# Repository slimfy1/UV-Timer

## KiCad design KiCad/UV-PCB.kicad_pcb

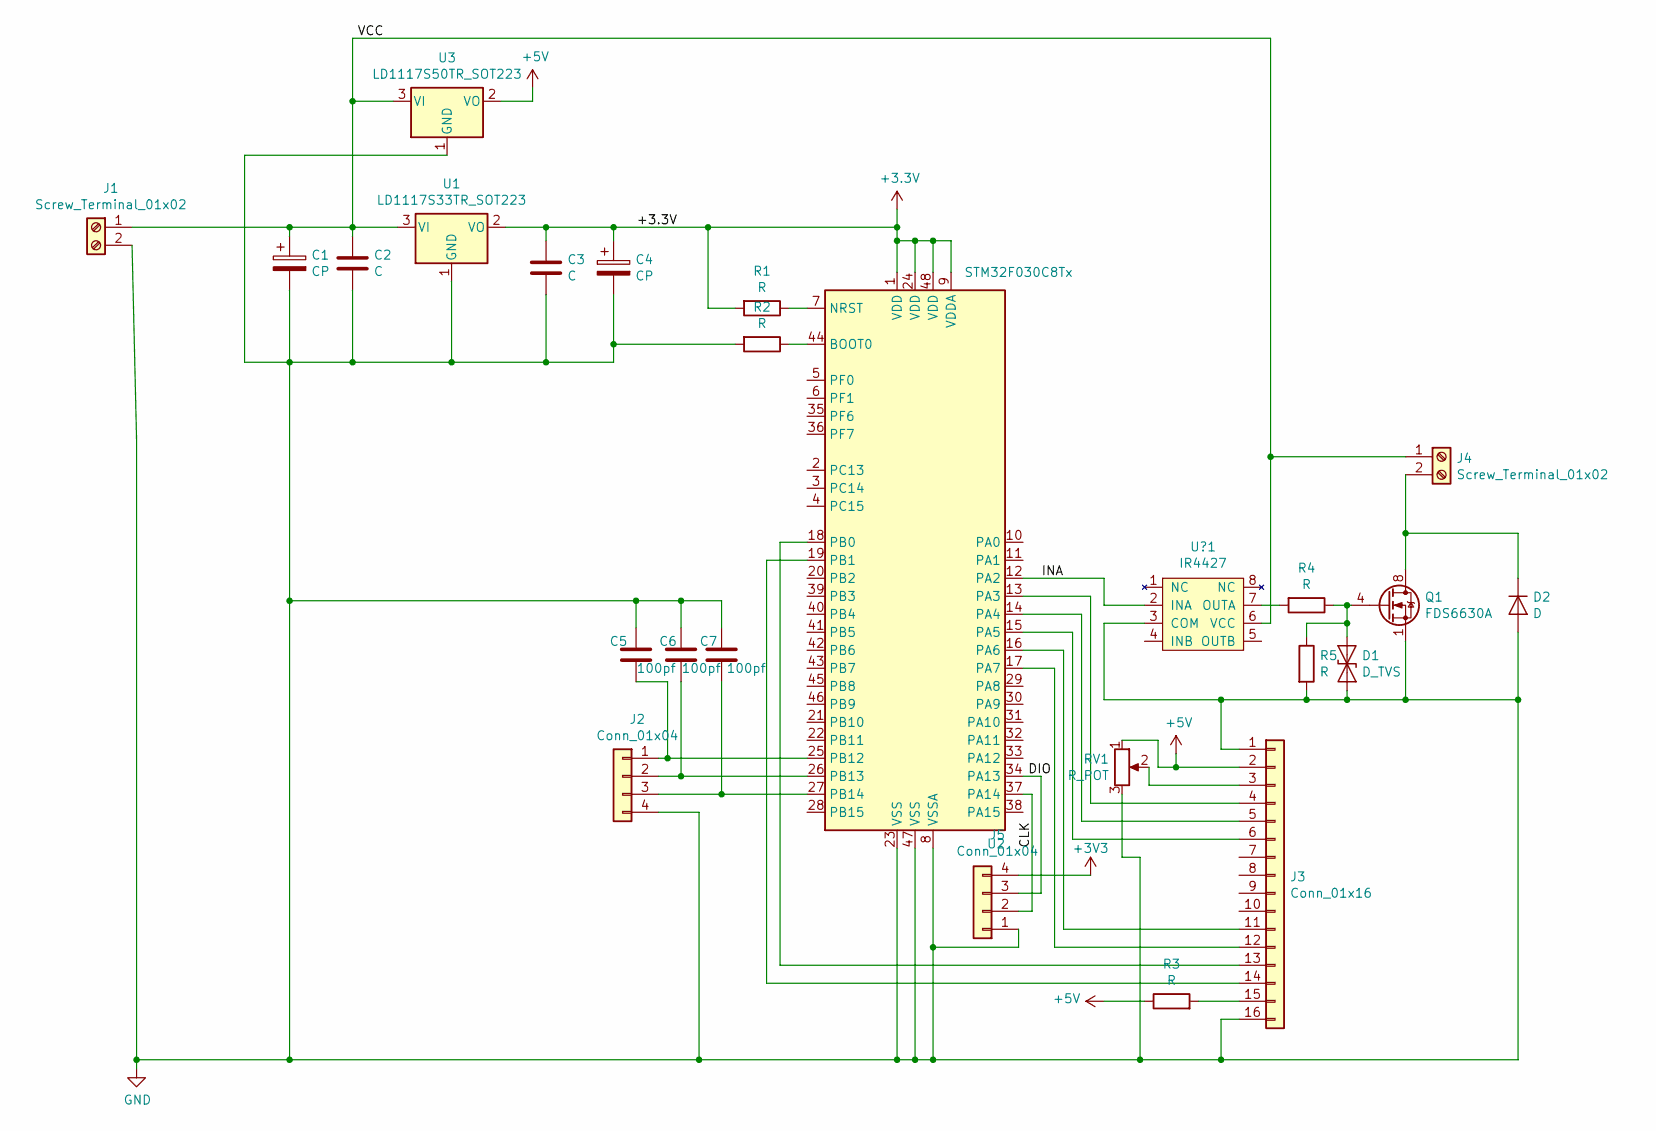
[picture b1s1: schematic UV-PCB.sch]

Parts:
C1, C4: CP; CP_EIA-3528-15_AVX-H
C2, C3: C; C_0805_2012Metric
C5, C6, C7: 100pf; C_0805_2012Metric
D1: D_TVS; D_SMB
D2: D; D_MiniMELF
J1, J4: Screw_Terminal_01x02; TerminalBlock_bornier-2_P5.08mm
J2: Conn_01x04; PinHeader_1x04_P2.54mm_Vertical
J3: Conn_01x16; PinHeader_1x16_P2.54mm_Vertical
J5: Conn_01x04; PinHeader_1x04_P2.54mm_Horizontal
Q1: FDS6630A; SOIC-8_3.9x4.9mm_P1.27mm
R1, R2, R3, R4, R5: R; R_0805_2012Metric
RV1: R_POT; Potentiometer_Bourns_3296W_Vertical
U1: LD1117S33TR_SOT223; TO-252-2
U2: STM32F030C8Tx; LQFP-48_7x7mm_P0.5mm
U3: LD1117S50TR_SOT223; TO-252-2
U?1: IR4427; IRS4427

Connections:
+5V: J3.2, R3.1, RV1.1, U3.2 (VO)
/CLK: J5.2, U2.37 (PA14)
/DIO: J5.3, U2.34 (PA13)
/INA: U2.12 (PA2), U?1.2 (INA)
/VCC: C1.1, C2.1, J1.1, J4.1, U1.3 (VI), U3.3 (VI), U?1.6 (VCC)
GND: C1.2, C2.2, C3.2, C4.2, C5.1, C6.1, C7.1, D1.2 (A2), D2.2 (A), J1.2, J2.4, J3.1, J3.16, J5.1, Q1.1 (S), Q1.2 (S), Q1.3 (S), R2.2, R5.2, RV1.3, U1.1 (GND), U2.8 (VSSA), U2.23 (VSS), U2.47 (VSS), U3.1 (GND), U?1.3 (COM)
unnamed: C5.2, J2.1, U2.25 (PB12)
unnamed: C6.2, J2.2, U2.26 (PB13)
unnamed: C7.2, J2.3, U2.27 (PB14)
unnamed: D1.1 (A1), Q1.4 (G), R4.1, R5.1
unnamed: D2.1 (K), J4.2, Q1.5 (D), Q1.6 (D), Q1.7 (D), Q1.8 (D)
unnamed: J3.3, RV1.2
unnamed: J3.4, U2.13 (PA3)
unnamed: J3.5, U2.14 (PA4)
unnamed: J3.6, U2.15 (PA5)
unnamed: J3.11, U2.16 (PA6)
unnamed: J3.12, U2.17 (PA7)
unnamed: J3.13, U2.18 (PB0)
unnamed: J3.14, U2.19 (PB1)
unnamed: J3.15, R3.2
unnamed: R1.1, U2.7 (NRST)
unnamed: R2.1, U2.44 (BOOT0)
unnamed: R4.2, U?1.7 (OUTA)

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
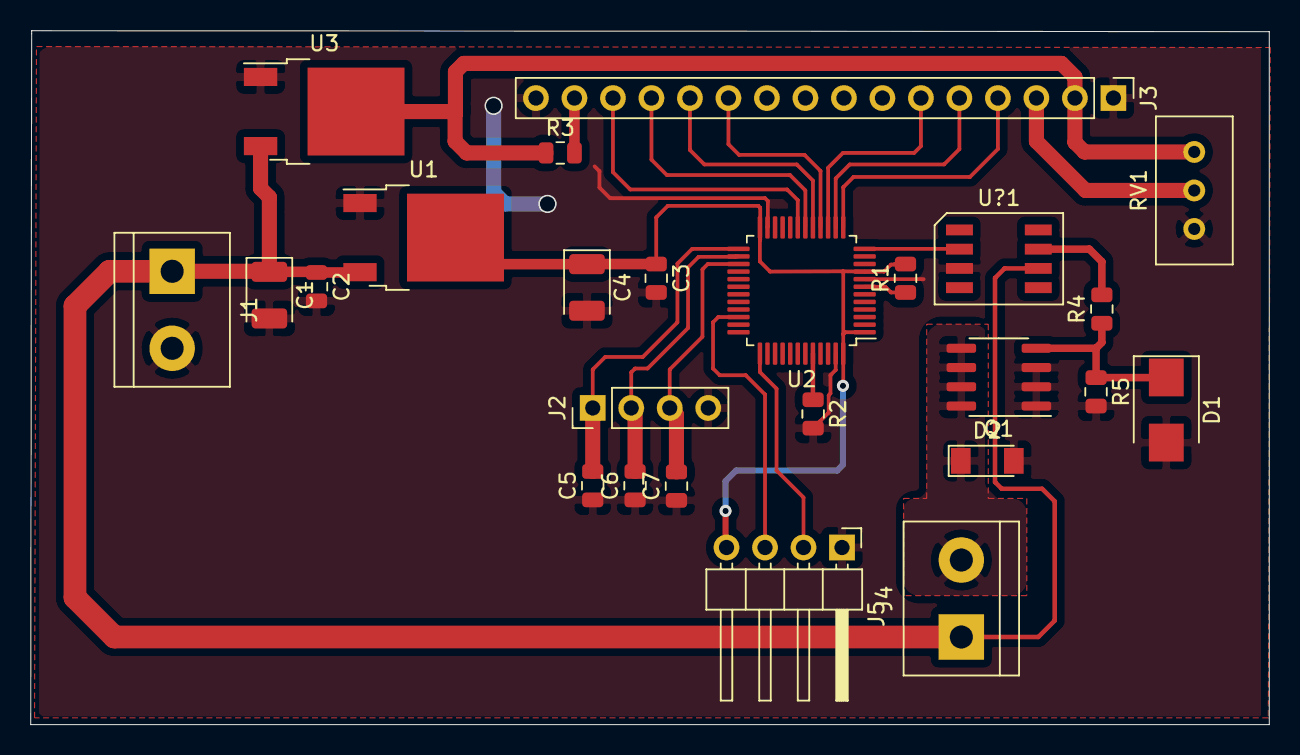
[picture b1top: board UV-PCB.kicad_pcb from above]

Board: 2 copper layers, 81.7 x 45.8 mm, 25 parts (0 on the bottom side), 24 nets.

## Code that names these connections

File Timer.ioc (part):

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PB14.GPIO_ModeDefaultEXTI=GPIO_MODE_IT_FALLING
PA6.GPIOParameters=GPIO_Label
PB13.GPIOParameters=GPIO_PuPd,GPIO_ModeDefaultEXTI
Mcu.UserName=STM32F103C8Tx
PA9.GPIO_Label=LED
PA9.GPIOParameters=GPIO_Label
PA3.GPIOParameters=GPIO_Label
PA6.GPIO_Label=D4
PB0.GPIO_Label=D6
PB13.Signal=GPXTI13
PB13.GPIO_ModeDefaultEXTI=GPIO_MODE_IT_FALLING
RCC.SYSCLKSource=RCC_SYSCLKSOURCE_PLLCLK
PA13.Signal=SYS_JTMS-SWDIO
PA9.Signal=GPIO_Output
PB14.Signal=GPXTI14
PA5.Signal=GPIO_Output
board=custom
PB13.GPIO_PuPd=GPIO_PULLUP
PB0.GPIOParameters=GPIO_Label
PA14.Mode=Serial_Wire
PB1.GPIO_Label=D7
PA4.GPIOParameters=GPIO_Label
PA13.Mode=Serial_Wire
Mcu.Name=STM32F103C(8-B)Tx
PA2.Signal=S_TIM2_CH3
PA4.Signal=GPIO_Output
RCC.SYSCLKFreq_VALUE=60000000
Mcu.Package=LQFP48
PA6.Signal=GPIO_Output
PB1.Signal=GPIO_Output
PB14.GPIO_PuPd=GPIO_PULLUP
PA7.GPIO_Label=D5
PA5.GPIO_Label=E
PA14.Signal=SYS_JTCK-SWCLK
PA5.GPIOParameters=GPIO_Label
PB14.GPIOParameters=GPIO_PuPd,GPIO_ModeDefaultEXTI
PB12.GPIO_ModeDefaultEXTI=GPIO_MODE_IT_FALLING
PB12.GPIO_PuPd=GPIO_PULLUP
PB0.Signal=GPIO_Output
PA4.GPIO_Label=RW
PA7.GPIOParameters=GPIO_Label
PB12.GPIOParameters=GPIO_PuPd,GPIO_ModeDefaultEXTI
PB12.Signal=GPXTI12
PB4.Signal=S_TIM3_CH1
PA3.GPIO_Label=RS
PA3.Signal=GPIO_Output
PB1.GPIOParameters=GPIO_Label
PA7.Signal=GPIO_Output

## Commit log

2020-06-03 Stable Release
2020-06-03 Create LICENCE
2020-07-05 Add PCB
2020-07-05 Add "Status" line on display
2020-07-05 Update for new PCB
